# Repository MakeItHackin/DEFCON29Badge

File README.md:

# DC 29 Badge and SAO
==========================================================

Purchase Fully Assembled Badge or Kit Here:  
https://www.tindie.com/products/makeithackin/makeithackin-def-con-29-electronic-badge/

Unboxing, Reviewing, and Programming a Fully-Assembled Badge:  
https://youtu.be/G82_usjS0wA

Assembling the badge kit:  
https://youtu.be/OIYtvjFRpec

I'll update this readme as time goes on, but yeah... this is my first official MakeItHackin unoffical DEF CON badge.

Badges will feature an ATTiny85 Microcontroller, OLED Display, RGB LEDs, and a SAO connector for all your shitty add-ons.

They will also include two security tags (applied in those blank spots).  One is for Checkpoint systems (8.2 MHz) and one is for Sensormatic systems (58 kHz).  Take your badge into any retail store and set off their alarms!  (just kidding, don't do that.)

It was difficult to think of a shape for the outline and I wanted to get them ordered ASAP, so I made the badge in the shape of a credit card to relate to the retail security theme.  

Hack the Planet

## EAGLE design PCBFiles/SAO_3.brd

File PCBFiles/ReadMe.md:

These are the Gerber Files used to make the PCBs.  Make your own!
The Eagle files are also included (.sch and .brd) for the Badge and SAO

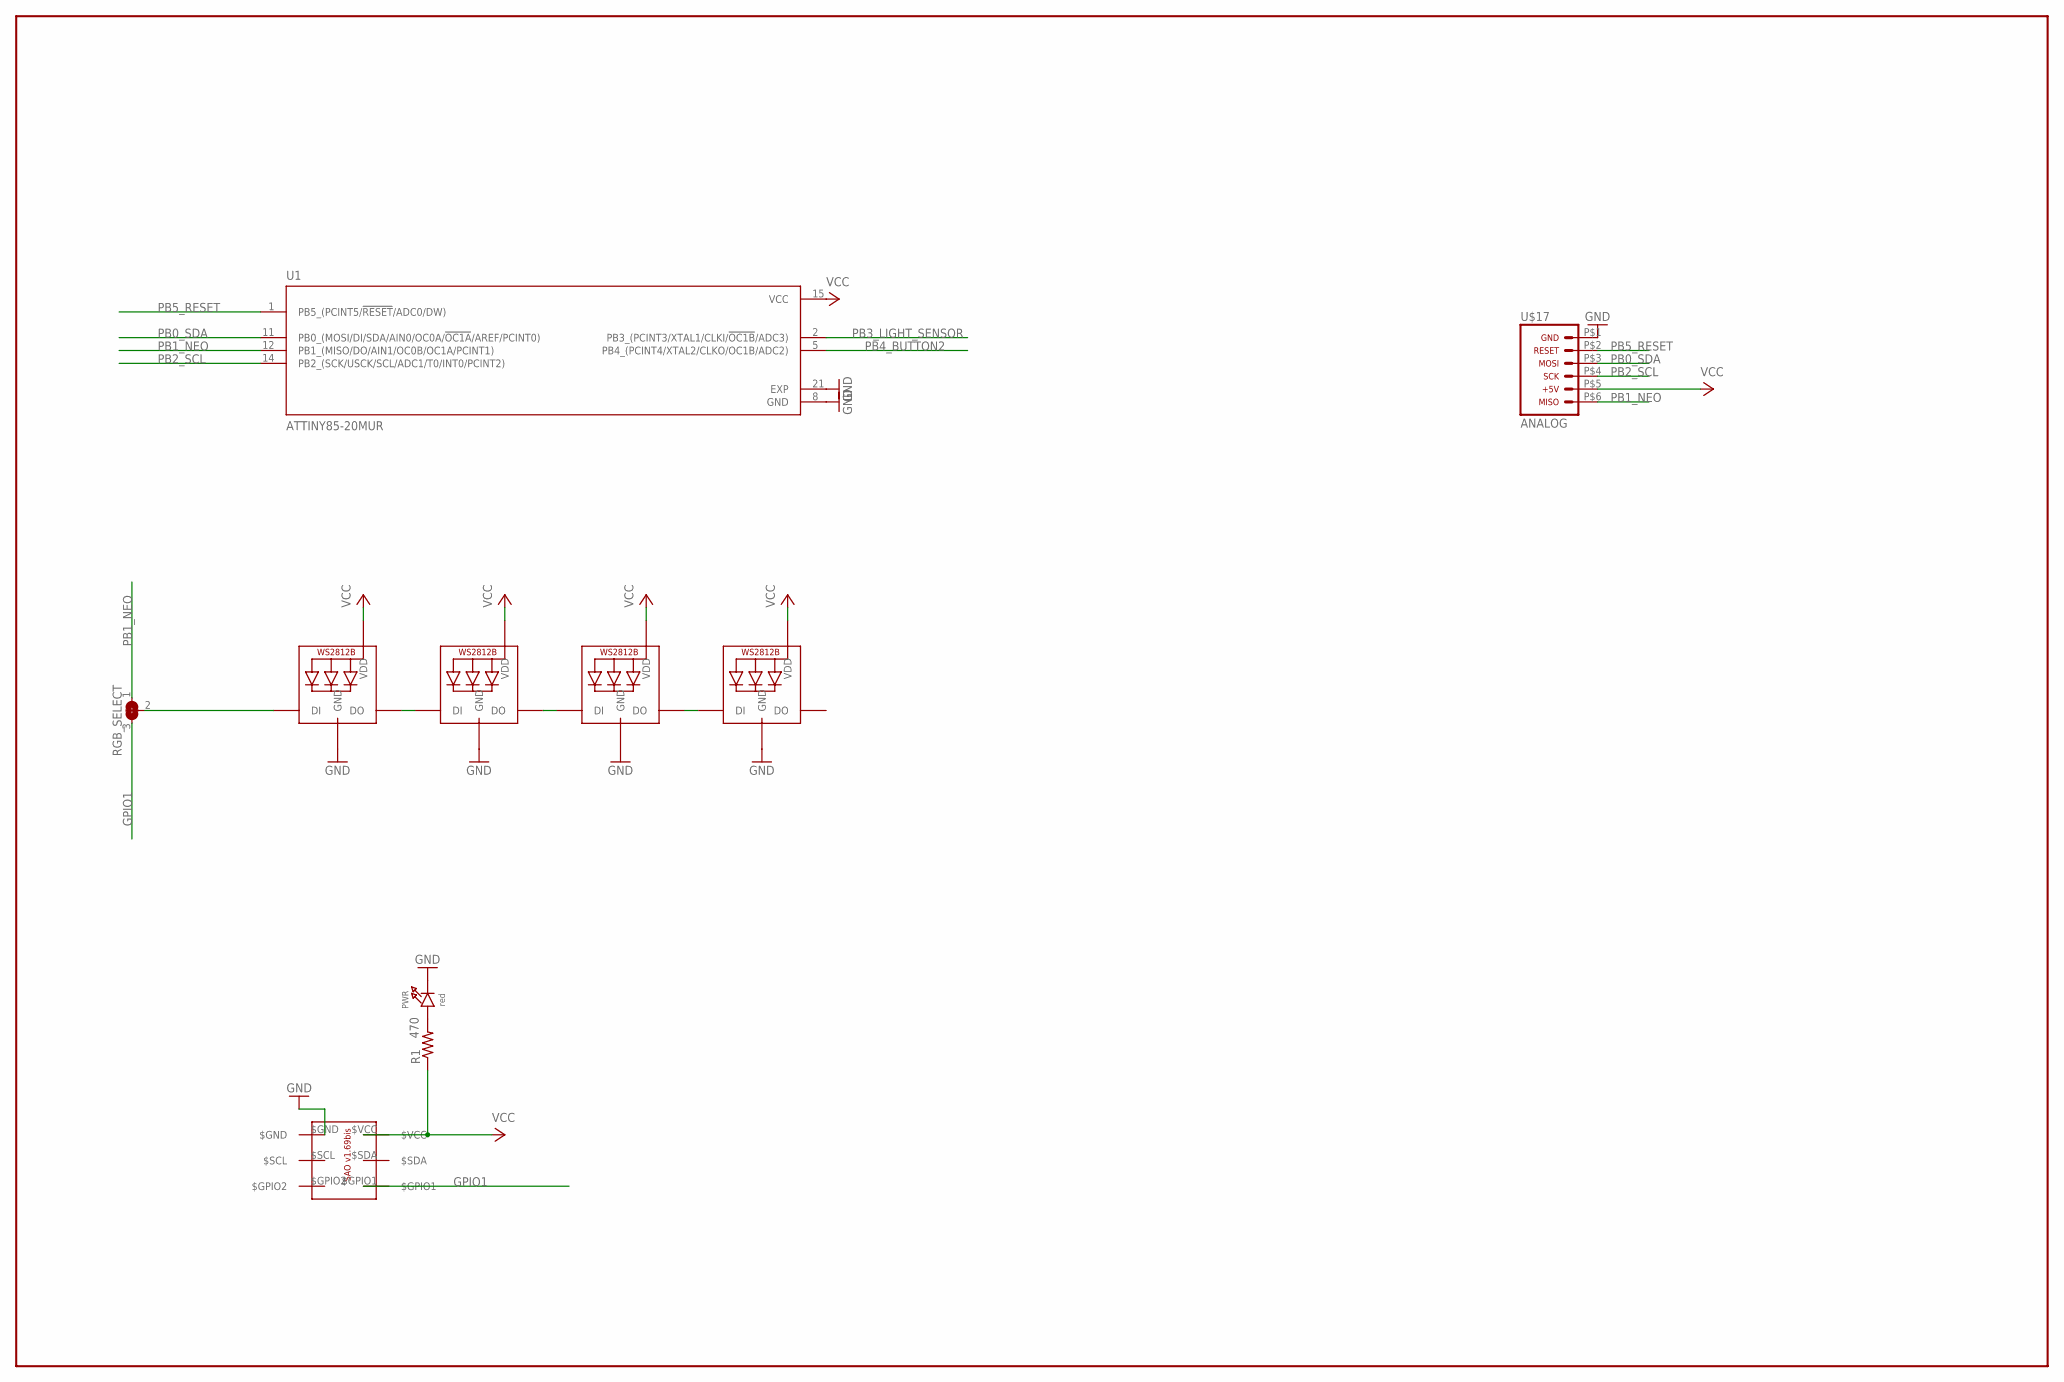
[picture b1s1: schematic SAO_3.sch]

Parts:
LED1, LED2, LED3, LED4: WS2812B3535; LED3535
PWR: red; CHIPLED_0805_NOOUTLINE
R1: 470; R0805
RGB_SELECT: SOLDERJUMPER_2WAY; SOLDERJUMPER_2WAY_OPEN_NOPASTE
U1: ATTINY85-20MUR; QFN50P400X400X80-21N
U$3: SAO-1.69; 2X3-SHROUDED-FEMALE
U$17: ICSP_FLATSMD_2X3; CONN-SMD-2X3

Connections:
GND: LED1.1 (GND), LED2.1 (GND), LED3.1 (GND), LED4.1 (GND), PWR.C, U1.8 (GND), U1.21 (EXP), U$3.$GND, U$17.P$1 (1)
GPIO1: RGB_SELECT.3, U$3.$GPIO1
unnamed: LED1.2 (DI), RGB_SELECT.2
unnamed: PWR.A, R1.2
unnamed: LED3.4 (DO), LED4.2 (DI)
unnamed: LED1.4 (DO), LED2.2 (DI)
unnamed: LED2.4 (DO), LED3.2 (DI)
PB0_SDA: U1.11 (PB0_(MOSI/DI/SDA/AIN0/OC0A/!OC1A!/AREF/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), U$17.P$3 (3)
PB1_NEO: RGB_SELECT.1, U1.12 (PB1_(MISO/DO/AIN1/OC0B/OC1A/PCINT1)), U$17.P$6 (6)
PB2_SCL: U1.14 (PB2_(SCK/USCK/SCL/ADC1/T0/INT0/PCINT2)), U$17.P$4 (4)
PB3_LIGHT_SENSOR: U1.2 (PB3_(PCINT3/XTAL1/CLKI/!OC1B!/ADC3))
PB4_BUTTON2: U1.5 (PB4_(PCINT4/XTAL2/CLKO/OC1B/ADC2))
PB5_RESET: U1.1 (PB5_(PCINT5/!RESET!/ADC0/DW)), U$17.P$2 (2)
VCC: LED1.3 (VDD), LED2.3 (VDD), LED3.3 (VDD), LED4.3 (VDD), R1.1, U1.15 (VCC), U$3.$VCC, U$17.P$5 (5)

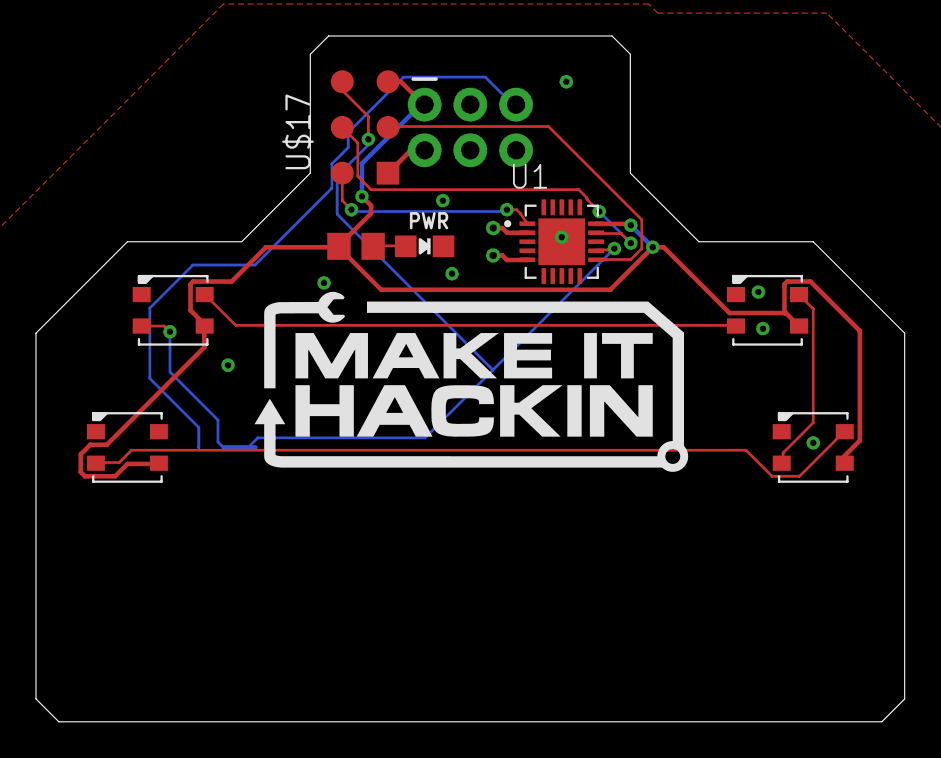
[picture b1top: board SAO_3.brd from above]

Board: 2 copper layers, 48.3 x 38.1 mm, 10 parts (1 on the bottom side), 12 nets.

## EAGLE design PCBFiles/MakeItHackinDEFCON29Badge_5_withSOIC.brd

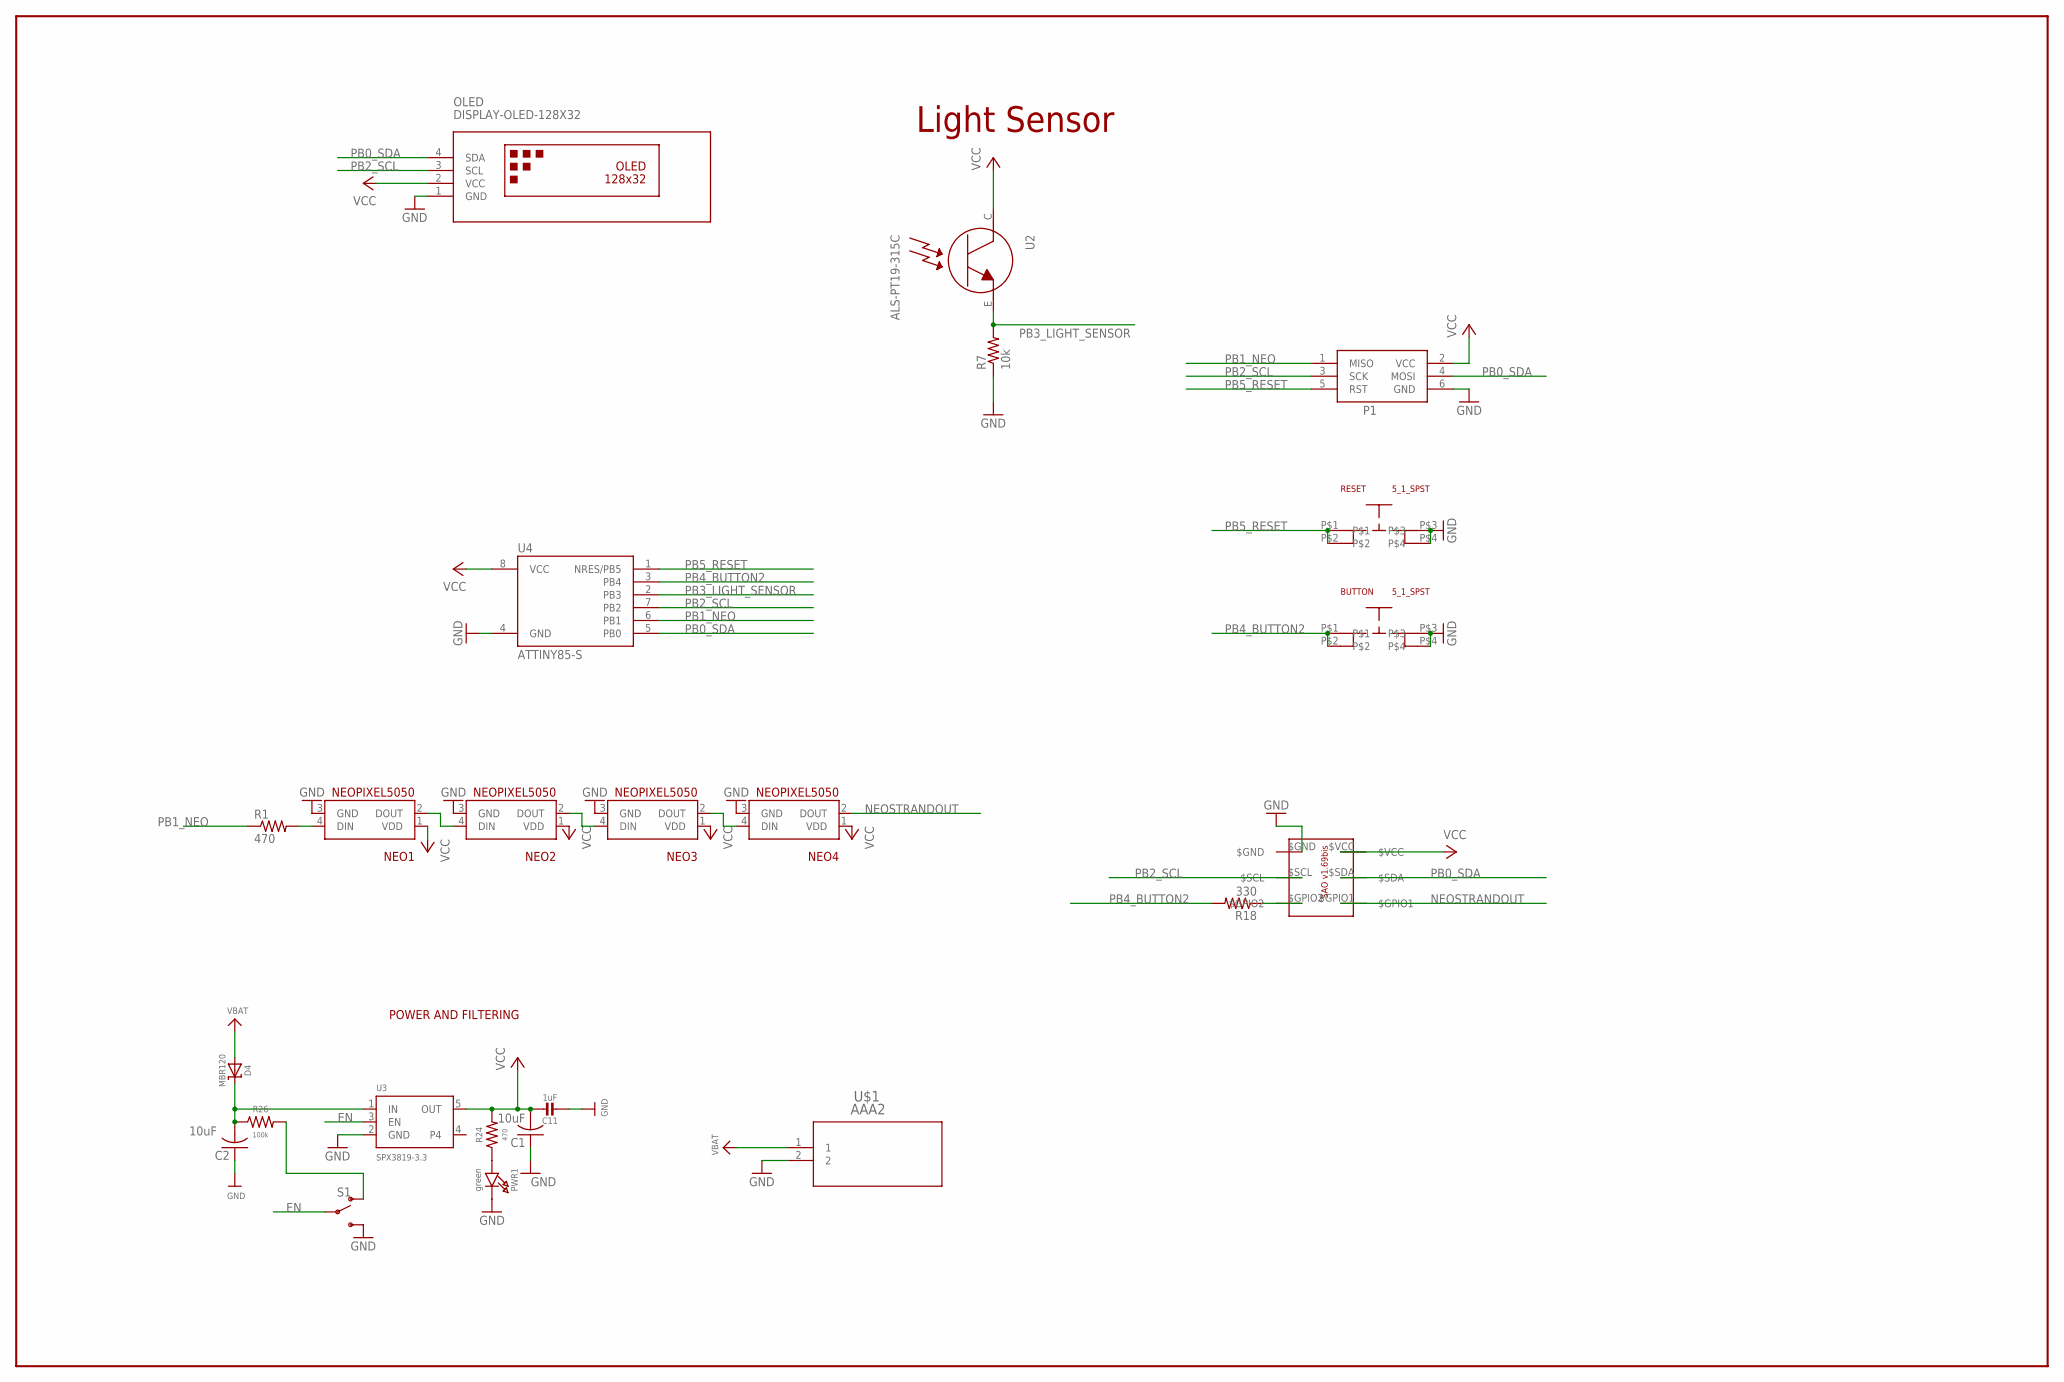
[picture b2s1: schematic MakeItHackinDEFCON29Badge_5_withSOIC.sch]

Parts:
BUTTON: 5_1_SPST
C1, C2: 10uF; C0805
C11: 1uF; 0805-NO@1
D4: MBR120; SOD-123
NEO1, NEO2, NEO3, NEO4: NEOPIXEL5050
OLED: DISPLAY-OLED-128X32
P1: AVRISP-6; AVRISP
PWR1: green; CHIPLED_0805_NOOUTLINE
R1, R24: 470; R0805
R7: 10k; R0805
R18: 330; R0805
R26: 100k; R0805
RESET: 5_1_SPST
S1: SWITCH-SPDT-SMD-AYZ0202; SWITCH_DPDT_SMD_AYZ0202
U2: ALS-PT19-315C
U3: SPX3819-3.3; SOT23-5
U4: ATTINY85-S; SOIC8_EIAJ_208MIL
U$1: AAA2
U$3: SAO-1.69; 2X3-SHROUDED-FEMALE

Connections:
EN: S1.2, U3.3 (EN)
GND: BUTTON.P$3, BUTTON.P$4, C1.1, C2.1, C11.2, NEO1.3 (GND), NEO2.3 (GND), NEO3.3 (GND), NEO4.3 (GND), OLED.1 (GND), P1.6 (GND), PWR1.C, R7.1, RESET.P$3, RESET.P$4, S1.3 (S), U3.2 (GND), U4.4 (GND), U$1.2, U$3.$GND
unnamed: C2.2, D4.C, R26.1, U3.1 (IN)
unnamed: R18.1, U$3.$GPIO2
unnamed: PWR1.A, R24.1
unnamed: R26.2, S1.1 (O)
unnamed: NEO1.4 (DIN), R1.2
unnamed: NEO1.2 (DOUT), NEO2.4 (DIN)
unnamed: NEO2.2 (DOUT), NEO3.4 (DIN)
unnamed: NEO3.2 (DOUT), NEO4.4 (DIN)
NEOSTRANDOUT: NEO4.2 (DOUT), U$3.$GPIO1
PB0_SDA: OLED.4 (SDA), P1.4 (MOSI), U4.5 (PB0), U$3.$SDA
PB1_NEO: P1.1 (MISO), R1.1, U4.6 (PB1)
PB2_SCL: OLED.3 (SCL), P1.3 (SCK), U4.7 (PB2), U$3.$SCL
PB3_LIGHT_SENSOR: R7.2, U2.E, U4.2 (PB3)
PB4_BUTTON2: BUTTON.P$1, BUTTON.P$2, R18.2, U4.3 (PB4)
PB5_RESET: P1.5 (RST), RESET.P$1, RESET.P$2, U4.1 (NRES/PB5)
VBAT: D4.A, U$1.1
VCC: C1.2, C11.1, NEO1.1 (VDD), NEO2.1 (VDD), NEO3.1 (VDD), NEO4.1 (VDD), OLED.2 (VCC), P1.2 (VCC), R24.2, U2.C, U3.5 (OUT), U4.8 (VCC), U$3.$VCC

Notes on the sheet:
Light Sensor
POWER AND FILTERING

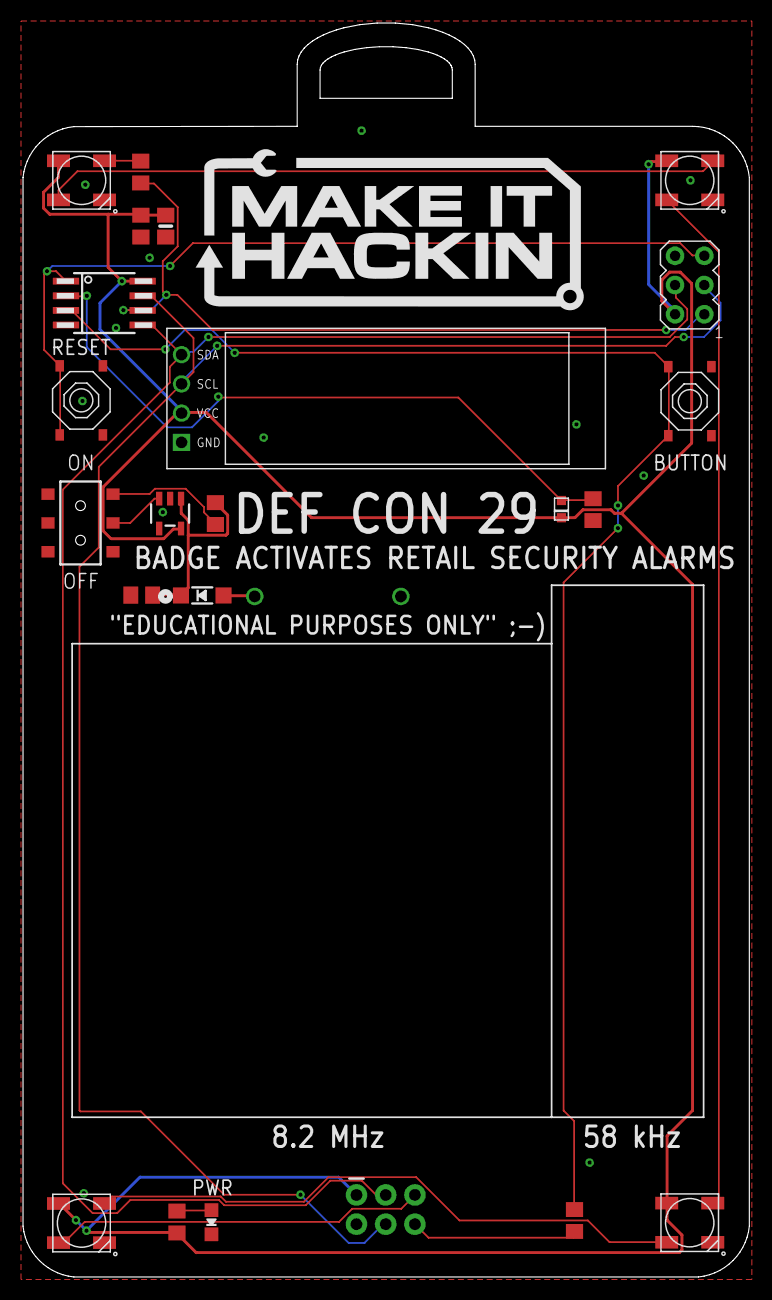
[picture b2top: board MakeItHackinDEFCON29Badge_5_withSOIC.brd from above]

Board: 2 copper layers, 63.1 x 109.0 mm, 24 parts (1 on the bottom side), 19 nets.

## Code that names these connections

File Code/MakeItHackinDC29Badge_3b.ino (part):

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  GND - BATTERY NEGATIVE TERMINAL
  VCC - BATTERY POSITIVE TERMINAL
  PBO - I2C BUS - SDA
  PB1 - NEOPIXEL OUT
  PB2 - I2C BUS - SCL
  PB3 - LIGHT SENSOR INPUT
  PB4 - BUTTON INPUT
  PB5 - RESET BUTTON
  
 */

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
                          

#define LIGHT_SENSOR_PIN A3  // THIS IS PB3, BUT MUST LABEL IT A3 IN ORDER FOR THE ANALOG FUNCTIONS TO WORK
int lightSensorValue = 0;

// 'makeithackin', 128x32px
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
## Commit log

2021-07-11 Create BOM
2021-07-15 Update BOM
2021-09-20 GerberFiles
2021-09-20 EagleFiles

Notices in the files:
Code/MakeItHackinDC29Badge_3b.ino:
MIT license, all text above must be included in any redistribution
parts and their libraries:
SparkFun-Switches: Licensing: Creative Commons ShareAlike 4.0 International - https://creativecommons.org/licenses/by-sa/4.0
microbuilder: This work is placed in the public domain, and may be freely used for commercial and non-commercial work with the following conditions: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
